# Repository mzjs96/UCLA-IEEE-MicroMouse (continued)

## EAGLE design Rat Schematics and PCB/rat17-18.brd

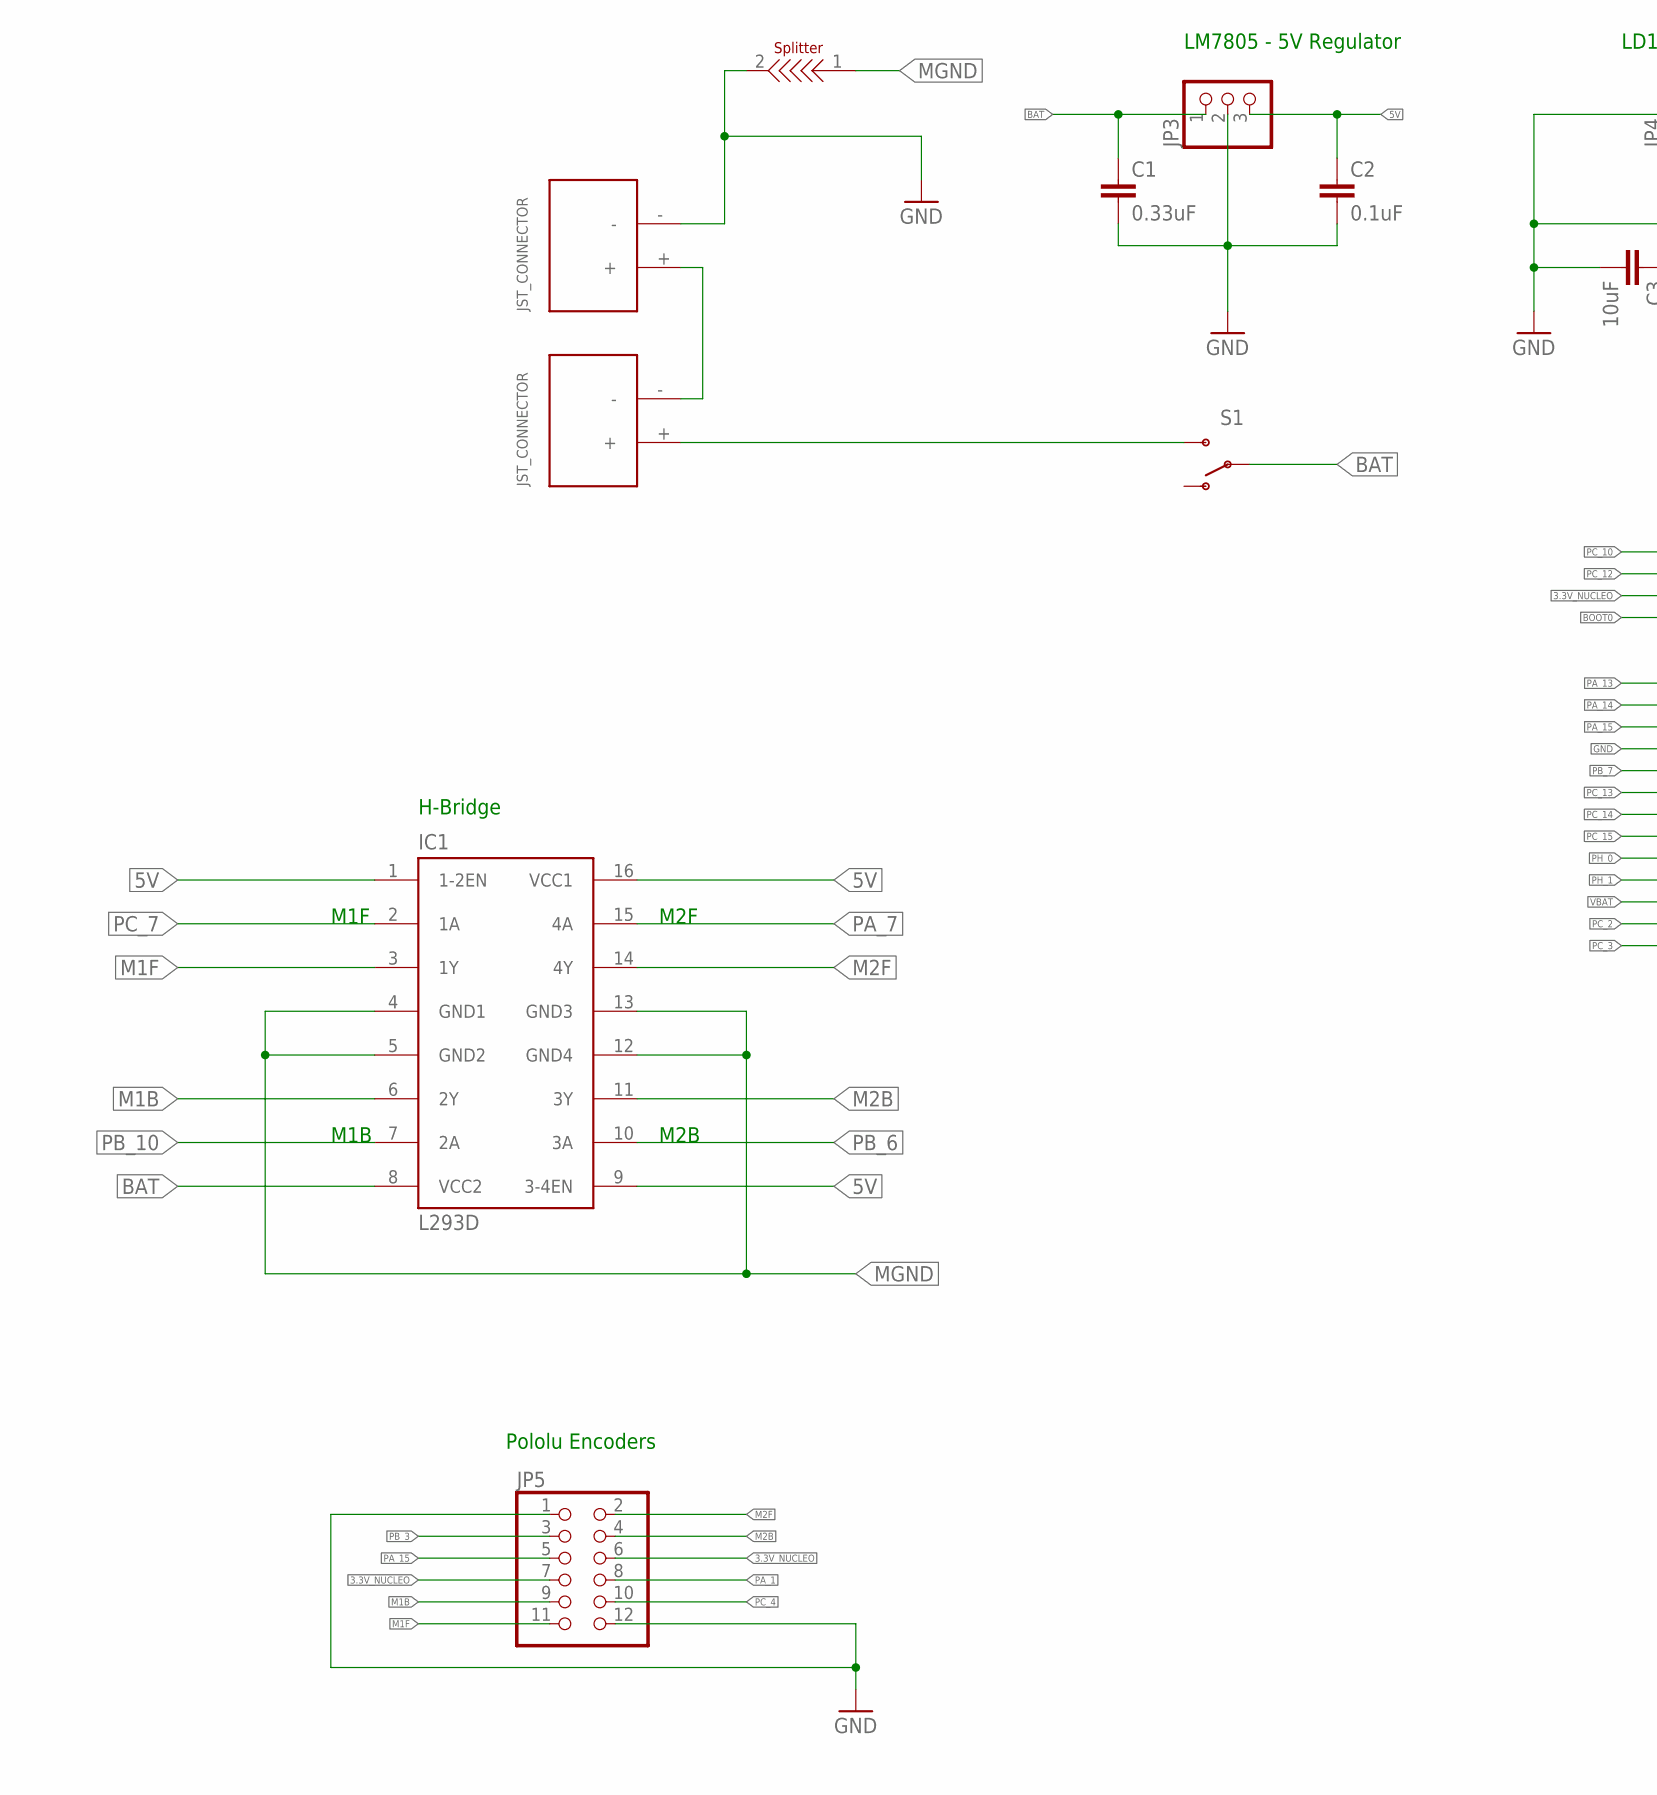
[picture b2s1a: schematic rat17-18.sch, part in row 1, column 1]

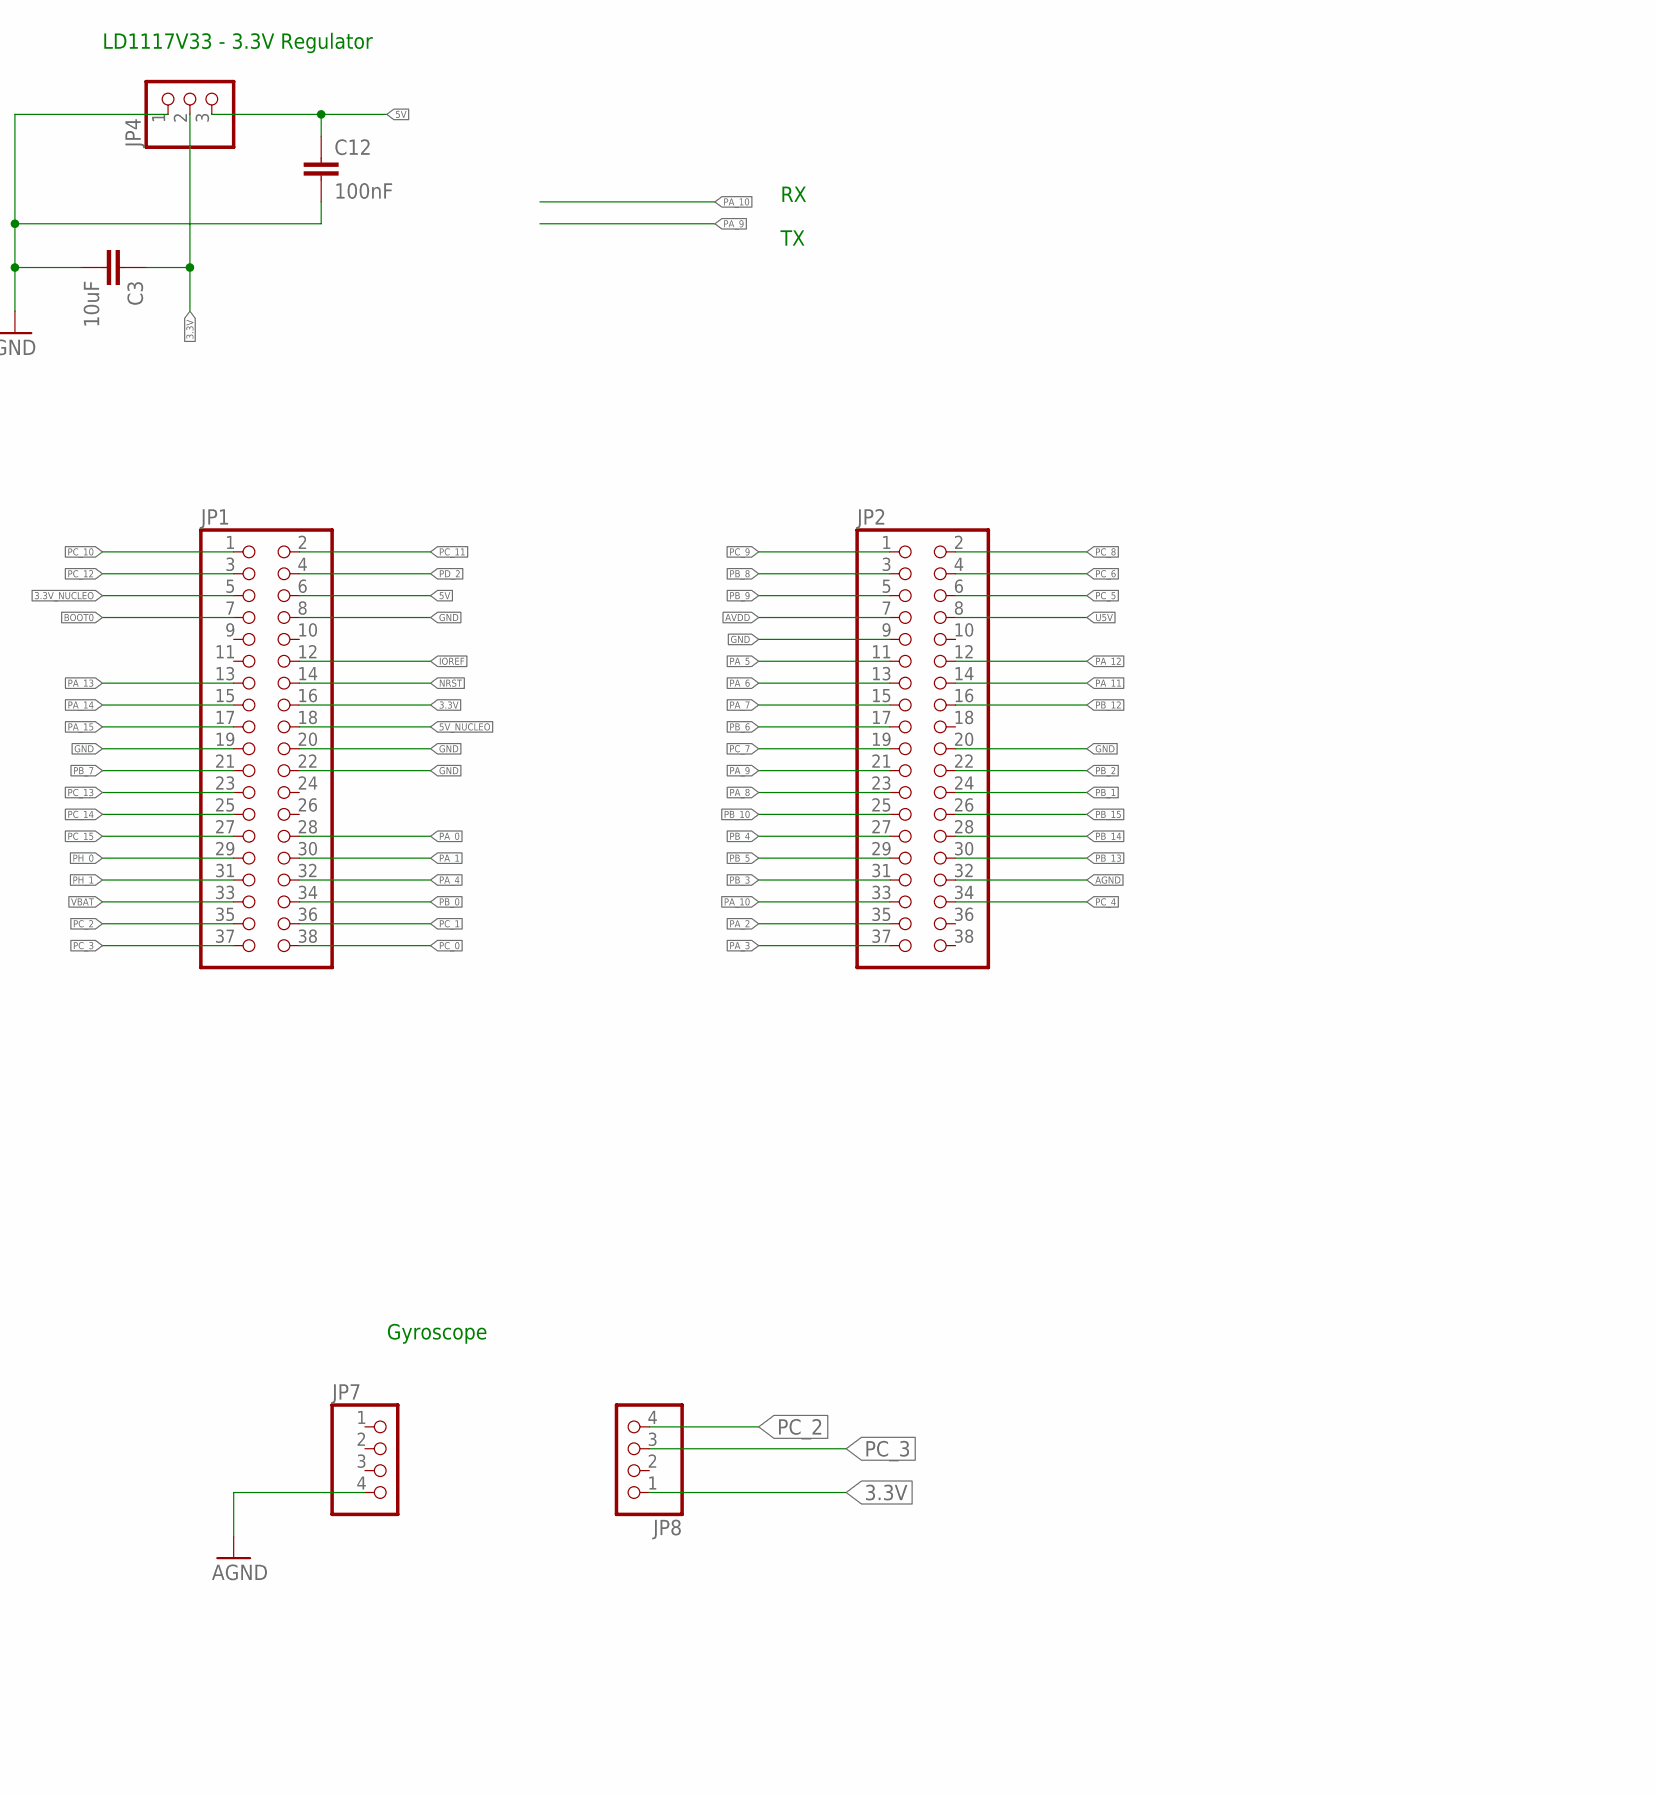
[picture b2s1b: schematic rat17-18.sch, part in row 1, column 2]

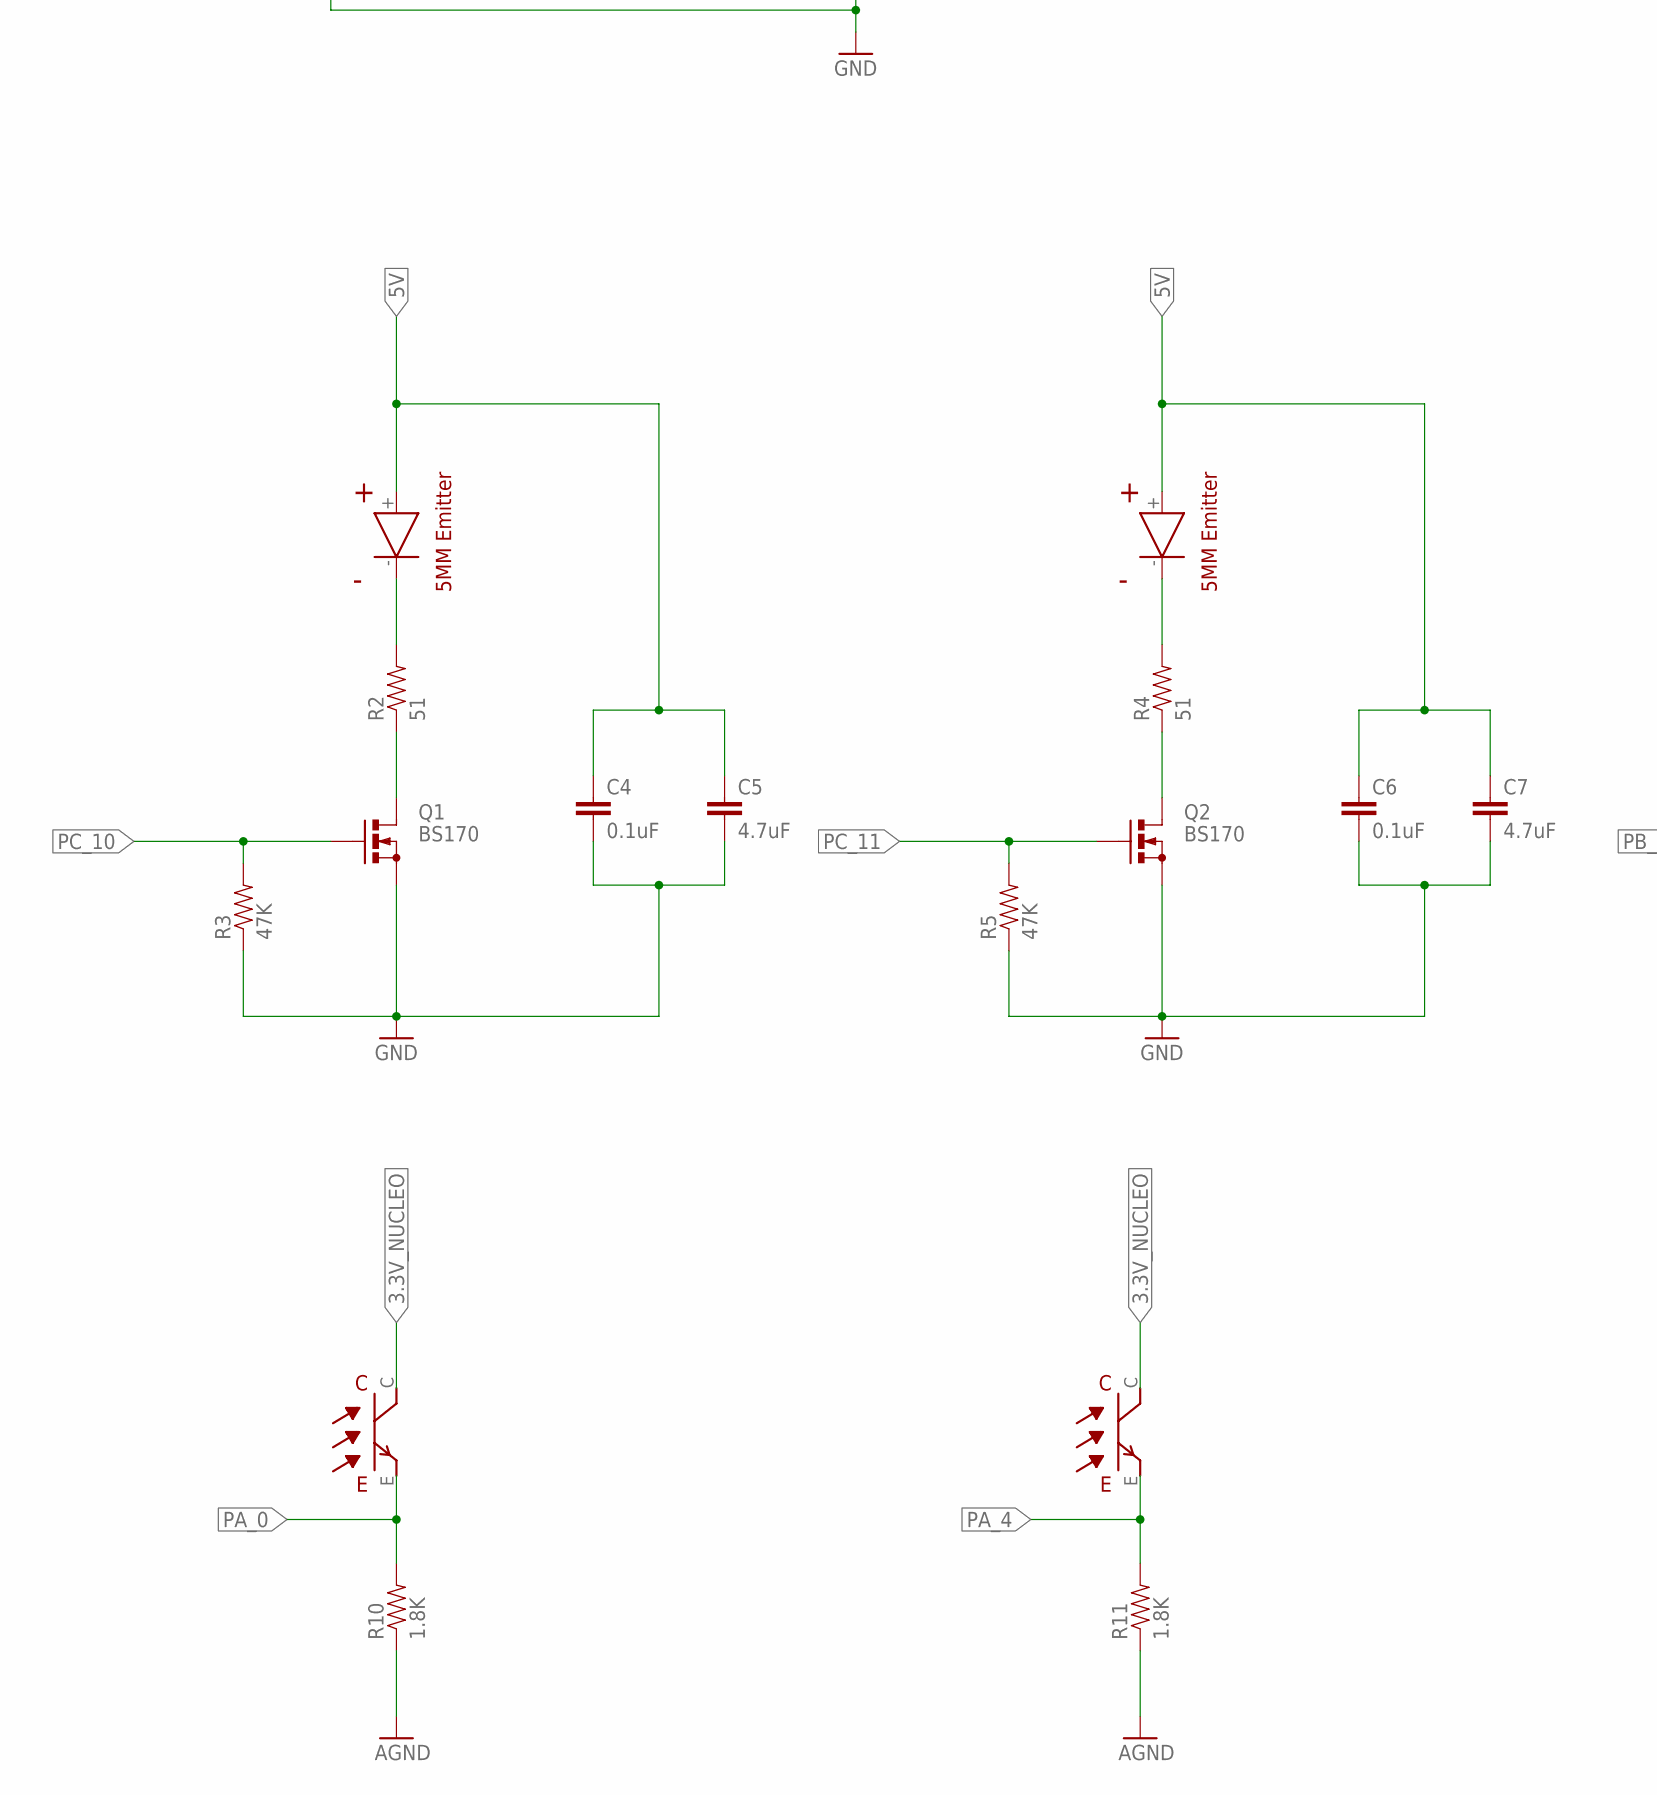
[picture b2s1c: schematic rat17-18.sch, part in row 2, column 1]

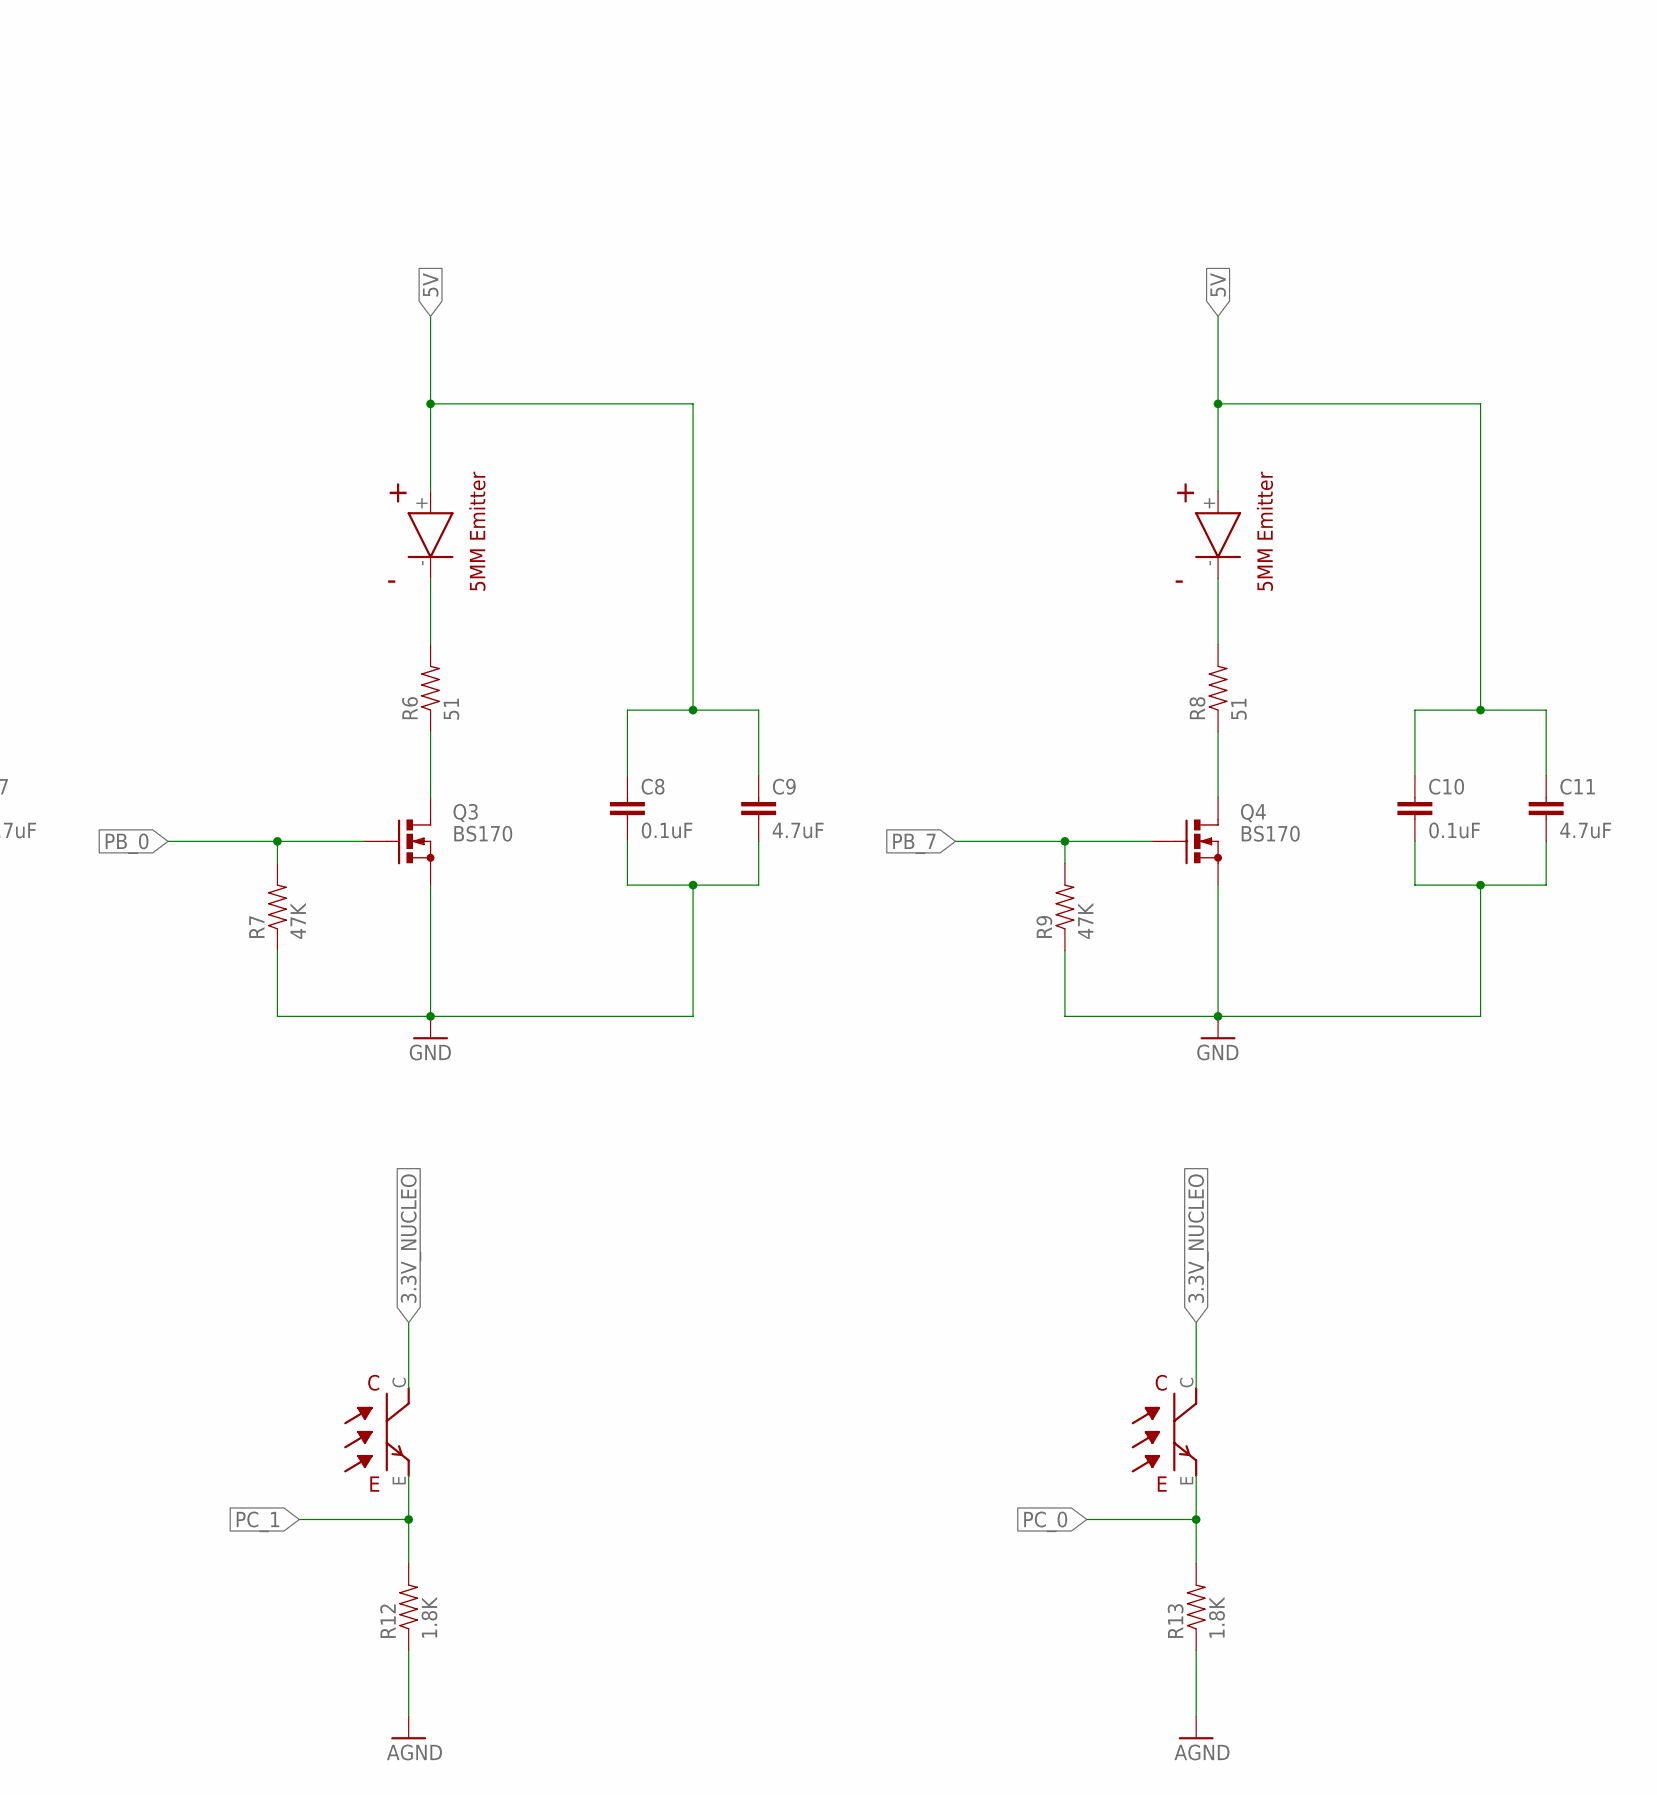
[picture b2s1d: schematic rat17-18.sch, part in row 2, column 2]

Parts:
C1: 0.33uF; AXIAL-5MM
C2, C4, C6, C8, C10: 0.1uF; AXIAL-5MM
C3: 10uF; AXIAL-5MM
C5, C7, C9, C11: 4.7uF; AXIAL-5MM
C12: 100nF; AXIAL-5MM
IC1: L293D; DIL16
JP1, JP2: PINHD-2X19; 2X19
JP3, JP4: PINHD-1X3; 1X03
JP5: PINHD-2X6; 2X06
JP7, JP8: PINHD-1X4; 1X04
Q1, Q2, Q3, Q4: BS170; SOT54E
R2, R4, R6, R8: 51; AXIAL-0.3
R3, R5, R7, R9: 47K; AXIAL-0.3
R10, R11, R12, R13: 1.8K; AXIAL-0.3
S1: SWITCH-SPSTPTH; SWITCH-SPDT
U$1, U$2: JST_CONNECTOR_FEMALE
U$3: SPLITTER
U$4, U$15, U$18, U$19: RECEIVER
U$5, U$6, U$7, U$8: EMITTER

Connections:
3.3V: C3.P$1 (1), JP1.16, JP4.2, JP8.1
3.3V_NUCLEO: JP1.5, JP5.6, JP5.7, U$4.C, U$15.C, U$18.C, U$19.C
5V: C2.P$1 (1), C4.P$1 (1), C5.P$1 (1), C6.P$1 (1), C7.P$1 (1), C8.P$1 (1), C9.P$1 (1), C10.P$1 (1), C11.P$1 (1), C12.P$1 (1), IC1.1 (1-2EN), IC1.9 (3-4EN), IC1.16 (VCC1), JP1.6, JP3.3, JP4.3, U$5.+, U$6.+, U$7.+, U$8.+
5V_NUCLEO: JP1.18
AGND: JP2.32, JP7.4, R10.P$1 (1), R11.P$1 (1), R12.P$1 (1), R13.P$1 (1)
AVDD: JP2.7
BAT: C1.P$1 (1), IC1.8 (VCC2), JP3.1, S1.2
BOOT0: JP1.7
GND: C1.P$2 (2), C2.P$2 (2), C3.P$2 (2), C4.P$2 (2), C5.P$2 (2), C6.P$2 (2), C7.P$2 (2), C8.P$2 (2), C9.P$2 (2), C10.P$2 (2), C11.P$2 (2), C12.P$2 (2), JP1.8, JP1.19, JP1.20, JP1.22, JP2.9, JP2.20, JP3.2, JP4.1, JP5.1, JP5.12, Q1.S, Q2.S, Q3.S, Q4.S, R3.P$1 (1), R5.P$1 (1), R7.P$1 (1), R9.P$1 (1), U$1.-, U$3.2
IOREF: JP1.12
M1B: IC1.6 (2Y), JP5.9
M1F: IC1.3 (1Y), JP5.11
M2B: IC1.11 (3Y), JP5.4
M2F: IC1.14 (4Y), JP5.2
MGND: IC1.4 (GND1), IC1.5 (GND2), IC1.12 (GND4), IC1.13 (GND3), U$3.1
unnamed: U$1.+, U$2.-
unnamed: R4.P$2 (2), U$6.-
unnamed: S1.3 (S), U$2.+
unnamed: R2.P$2 (2), U$5.-
unnamed: Q1.D, R2.P$1 (1)
unnamed: Q2.D, R4.P$1 (1)
unnamed: R6.P$2 (2), U$7.-
unnamed: Q3.D, R6.P$1 (1)
unnamed: R8.P$2 (2), U$8.-
unnamed: Q4.D, R8.P$1 (1)
NRST: JP1.14
PA_0: JP1.28, R10.P$2 (2), U$19.E
PA_1: JP1.30, JP5.8
PA_2: JP2.35
PA_3: JP2.37
PA_4: JP1.32, R11.P$2 (2), U$18.E
PA_5: JP2.11
PA_6: JP2.13
PA_7: IC1.15 (4A), JP2.15
PA_8: JP2.23
PA_9: JP2.21
PA_10: JP2.33
PA_11: JP2.14
PA_12: JP2.12
PA_13: JP1.13
PA_14: JP1.15
PA_15: JP1.17, JP5.5
PB_0: JP1.34, Q3.G, R7.P$2 (2)
PB_1: JP2.24
PB_2: JP2.22
PB_3: JP2.31, JP5.3
PB_4: JP2.27
PB_5: JP2.29
PB_6: IC1.10 (3A), JP2.17
PB_7: JP1.21, Q4.G, R9.P$2 (2)
PB_8: JP2.3
PB_9: JP2.5
PB_10: IC1.7 (2A), JP2.25
PB_12: JP2.16
PB_13: JP2.30
PB_14: JP2.28
PB_15: JP2.26
PC_0: JP1.38, R13.P$2 (2), U$4.E
PC_1: JP1.36, R12.P$2 (2), U$15.E
PC_2: JP1.35, JP8.4
PC_3: JP1.37, JP8.3
PC_4: JP2.34, JP5.10
PC_5: JP2.6
PC_6: JP2.4
PC_7: IC1.2 (1A), JP2.19
PC_8: JP2.2
PC_9: JP2.1
PC_10: JP1.1, Q1.G, R3.P$2 (2)
PC_11: JP1.2, Q2.G, R5.P$2 (2)
PC_12: JP1.3
PC_13: JP1.23
PC_14: JP1.25
PC_15: JP1.27
PD_2: JP1.4
PH_0: JP1.29
PH_1: JP1.31
U5V: JP2.8
VBAT: JP1.33

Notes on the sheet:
LM7805 - 5V Regulator
LD1117V33 - 3.3V Regulator
H-Bridge
M1F
M1B
M2F
M2B
Pololu Encoders
Gyroscope

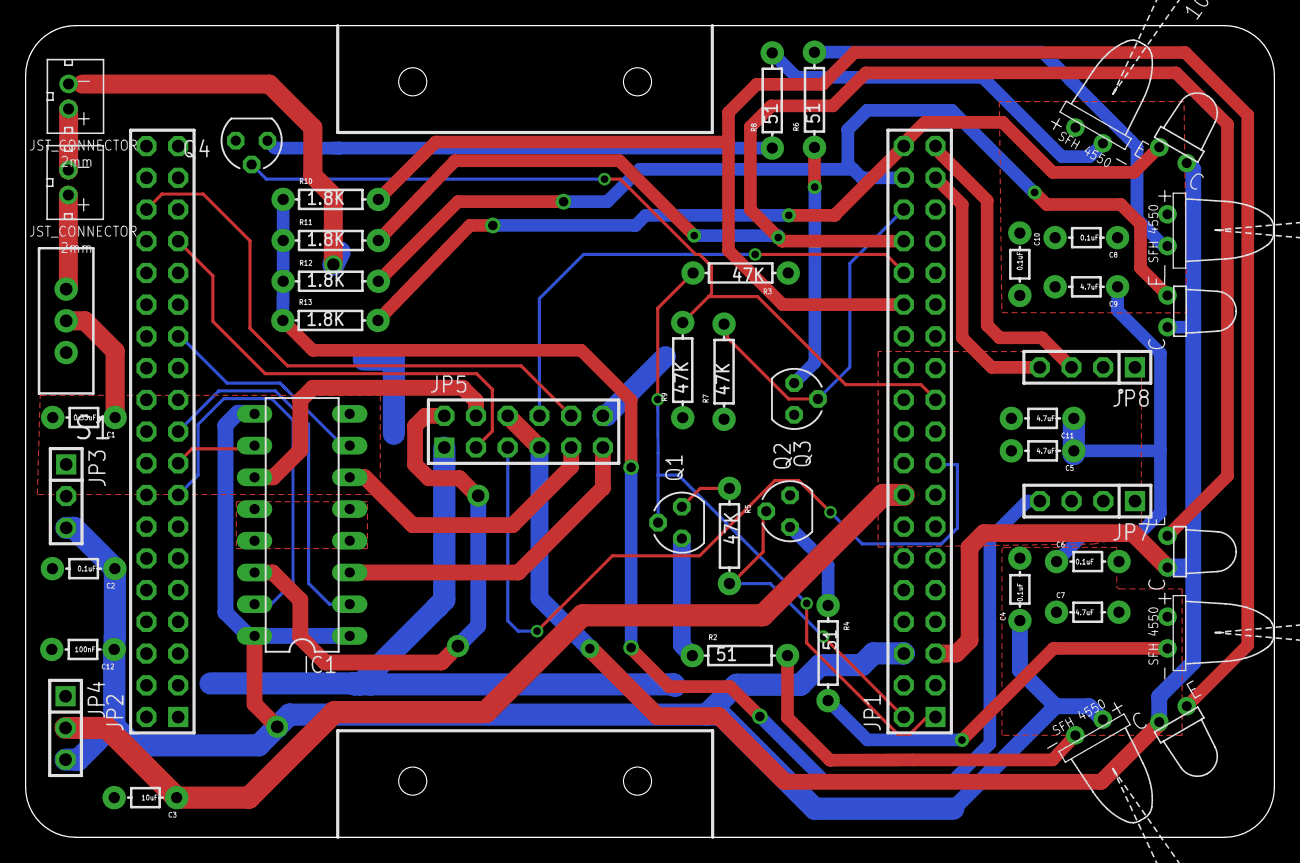
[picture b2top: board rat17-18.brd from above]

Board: 2 copper layers, 100.0 x 65.0 mm, 48 parts (0 on the bottom side), 39 nets.

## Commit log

2018-02-13 Fall 2017 Nucleus Rat
2018-02-13 Mouse PCB and Schematic
